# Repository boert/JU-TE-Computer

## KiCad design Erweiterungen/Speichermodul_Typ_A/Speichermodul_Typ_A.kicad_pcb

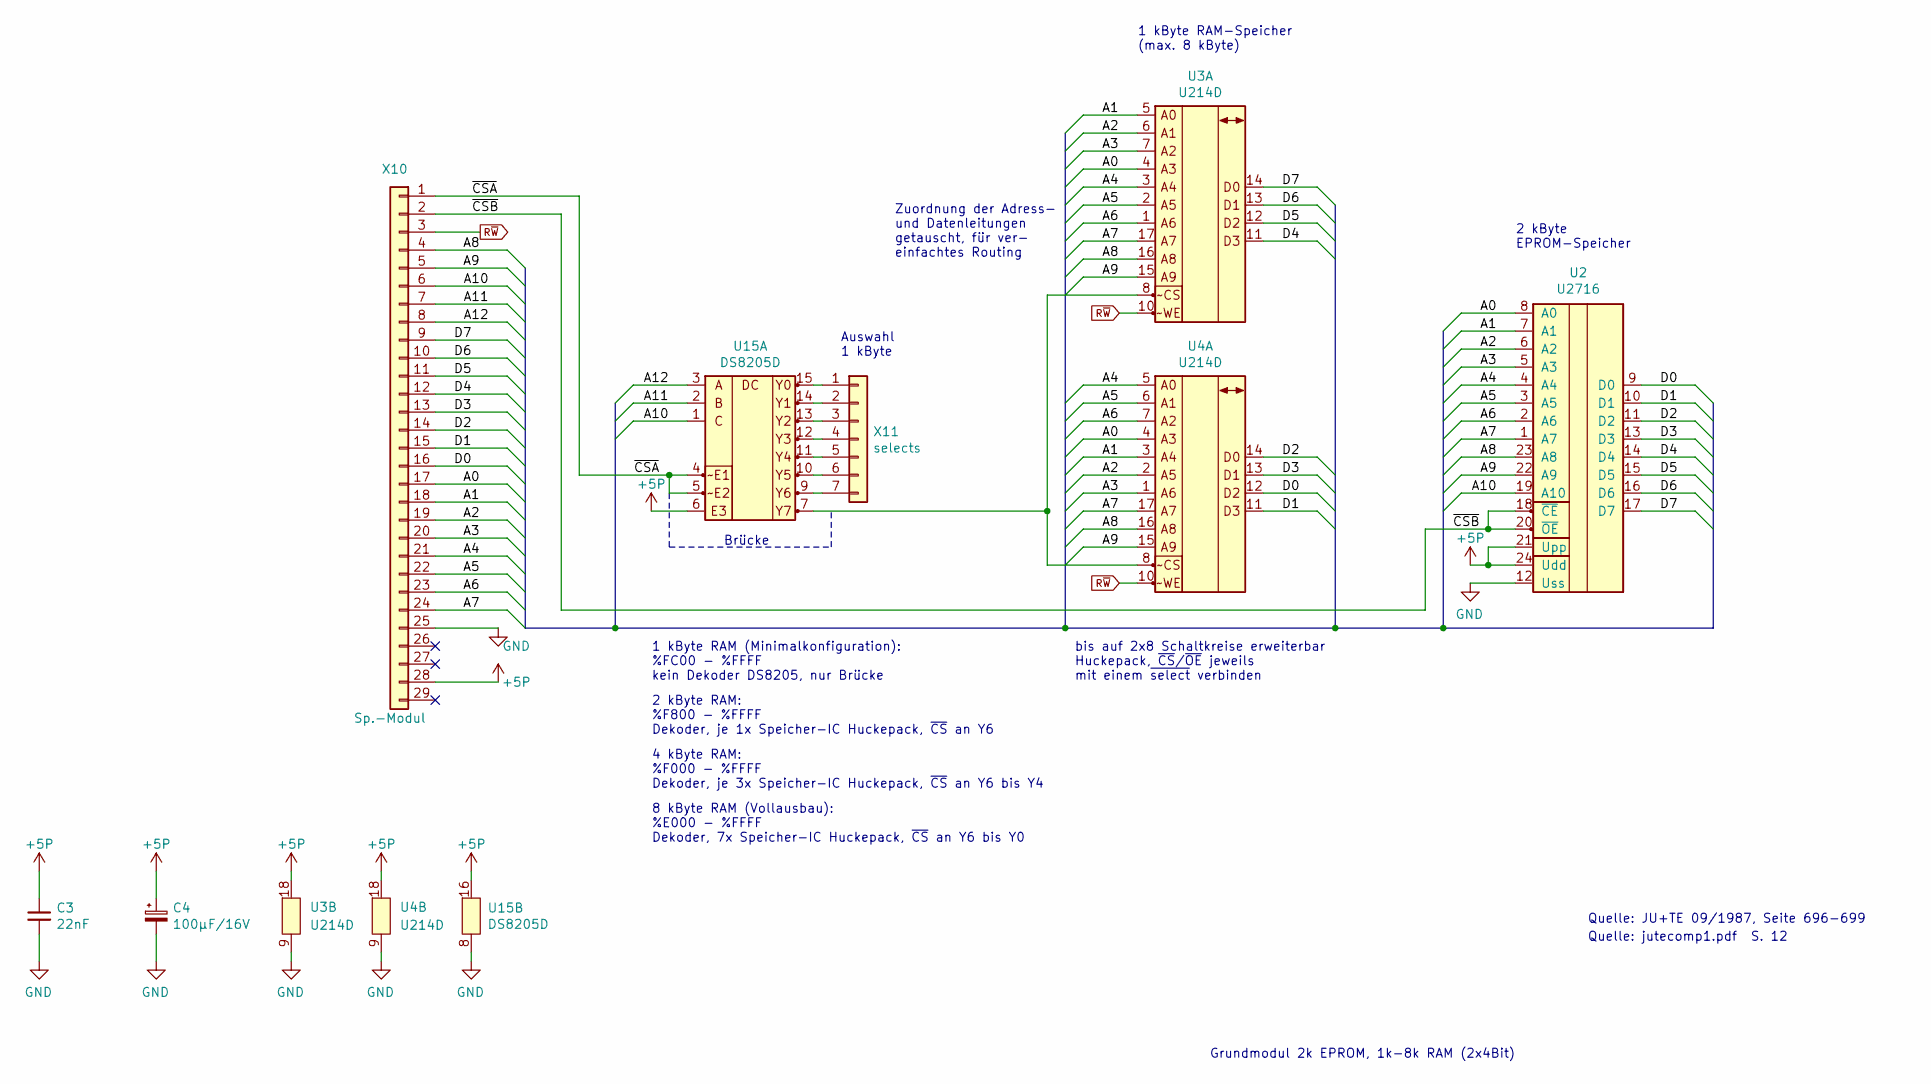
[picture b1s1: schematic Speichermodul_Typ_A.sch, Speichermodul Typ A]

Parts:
C3: 22nF; C_Disc_D4.3mm_W1.9mm_P5.00mm
C4: 100µF/16V; CP_Radial_D10.0mm_P3.50mm
U2: U2716; DIP-24_W15.24mm_Socket
U3, U4: U214D; DIP-18_W7.62mm_Socket
U15: DS8205D; DIP-16_W7.62mm_Socket
X10: Sp.-Modul; PinHeader_1x29_P2.54mm_Horizontal
X11: selects; PinSocket_1x07_P2.54mm_Vertical

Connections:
+5P: C3.1, C4.1, U2.21 (Upp), U2.24 (Udd), U3.18 (Udd), U4.18 (Udd), U15.6 (E3), U15.16 (Vcc), X10.28
/A0: U2.8 (A0), U3.4 (A3), U4.4 (A3), X10.17
/A1: U2.7 (A1), U3.5 (A0), U4.3 (A4), X10.18
/A2: U2.6 (A2), U3.6 (A1), U4.2 (A5), X10.19
/A3: U2.5 (A3), U3.7 (A2), U4.1 (A6), X10.20
/A4: U2.4 (A4), U3.3 (A4), U4.5 (A0), X10.21
/A5: U2.3 (A5), U3.2 (A5), U4.6 (A1), X10.22
/A6: U2.2 (A6), U3.1 (A6), U4.7 (A2), X10.23
/A7: U2.1 (A7), U3.17 (A7), U4.17 (A7), X10.24
/A8: U2.23 (A8), U3.16 (A8), U4.16 (A8), X10.4
/A9: U2.22 (A9), U3.15 (A9), U4.15 (A9), X10.5
/A10: U2.19 (A10), U15.1 (C), X10.6
/A11: U15.2 (B), X10.7
/A12: U15.3 (A), X10.8
/D0: U2.9 (D0), U4.12 (D2), X10.16
/D1: U2.10 (D1), U4.11 (D3), X10.15
/D2: U2.11 (D2), U4.14 (D0), X10.14
/D3: U2.13 (D3), U4.13 (D1), X10.13
/D4: U2.14 (D4), U3.11 (D3), X10.12
/D5: U2.15 (D5), U3.12 (D2), X10.11
/D6: U2.16 (D6), U3.13 (D1), X10.10
/D7: U2.17 (D7), U3.14 (D0), X10.9
/~CSA: U15.4 (~E1), U15.5 (~E2), X10.1
GND: C3.2, C4.2, U2.12 (Uss), U3.9 (Uss), U4.9 (Uss), U15.8 (GND), X10.25
unnamed: U3.8 (~CS), U4.8 (~CS), U15.7 (Y7)
unnamed: U15.9 (Y6), X11.7
unnamed: U15.10 (Y5), X11.6
unnamed: U15.11 (Y4), X11.5
unnamed: U15.12 (Y3), X11.4
unnamed: U15.13 (Y2), X11.3
unnamed: U15.14 (Y1), X11.2
unnamed: U15.15 (Y0), X11.1
R~W: U3.10 (~WE), U4.10 (~WE), X10.3
~CSB: U2.18 (~CE), U2.20 (~OE), X10.2

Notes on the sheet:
Zuordnung der Adress- und Datenleitungen getauscht, für ver- einfachtes Routing
Brücke
Quelle: JU+TE 09/1987, Seite 696-699
Quelle: jutecomp1.pdf S. 12
1 kByte RAM (Minimalkonfiguration): %FC00 - %FFFF kein Dekoder DS8205, nur Brücke
2 kByte RAM: %F800 - %FFFF Dekoder, je 1x Speicher-IC Huckepack, ~CS~ an Y6
Auswahl 1 kByte
8 kByte RAM (Vollausbau): %E000 - %FFFF Dekoder, 7x Speicher-IC Huckepack, ~CS~ an Y6 bis Y0
4 kByte RAM: %F000 - %FFFF Dekoder, je 3x Speicher-IC Huckepack, ~CS~ an Y6 bis Y4
1 kByte RAM-Speicher (max. 8 kByte)
bis auf 2x8 Schaltkreise erweiterbar Huckepack, ~CS~/~OE~ jeweils mit einem ~select~ verbinden
2 kByte EPROM-Speicher
Grundmodul 2k EPROM, 1k-8k RAM (2x4Bit)

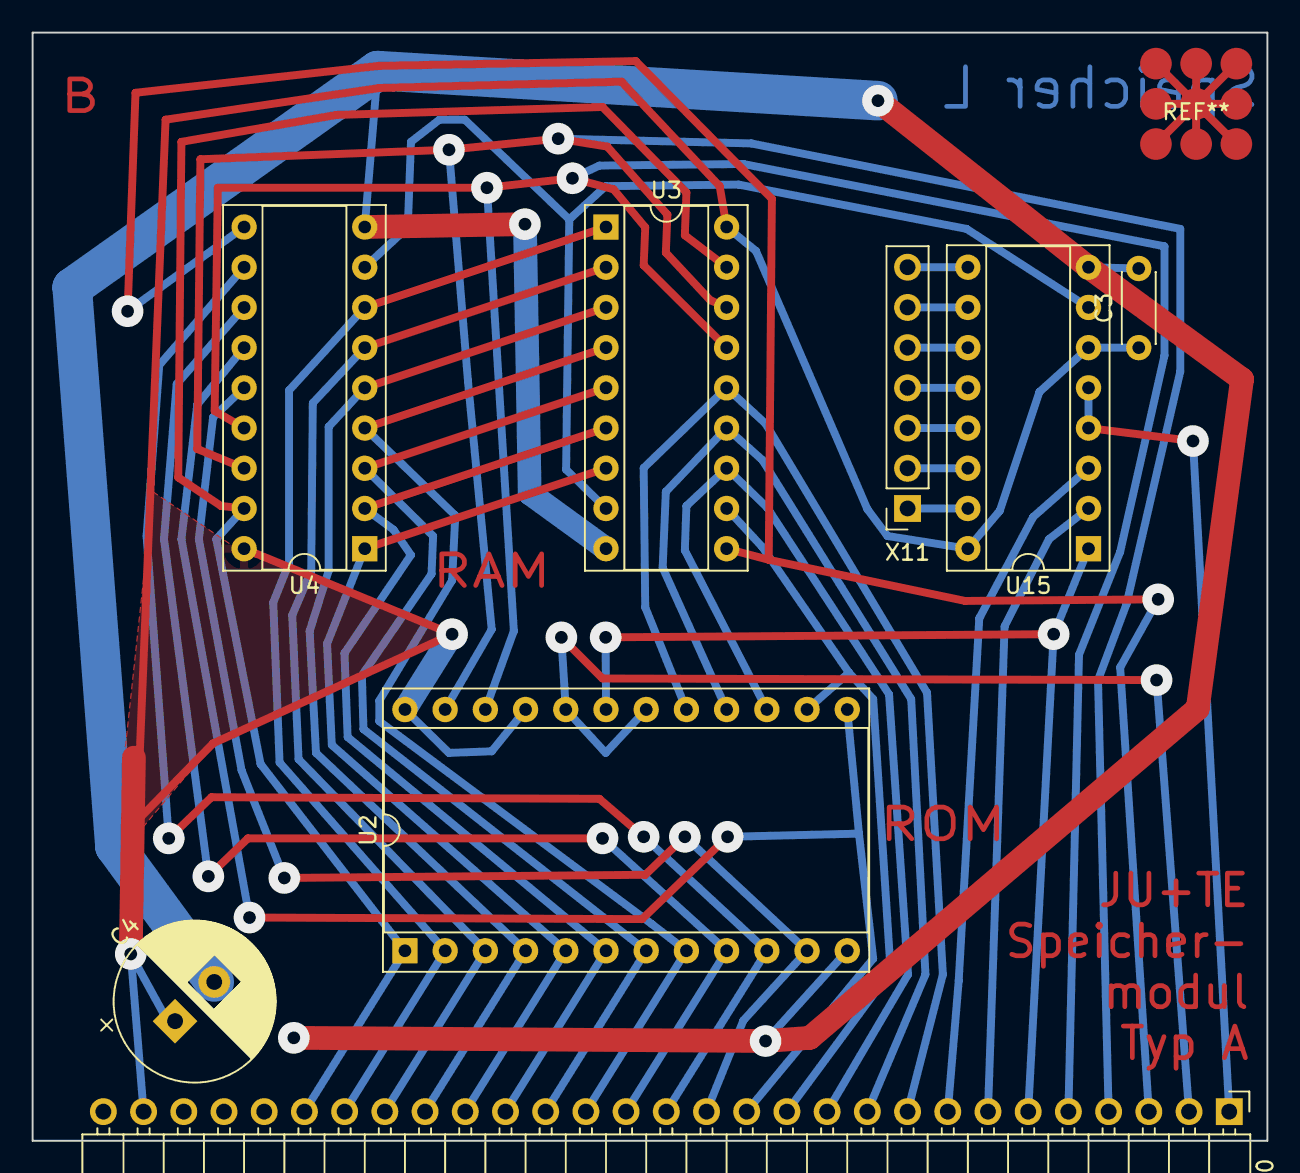
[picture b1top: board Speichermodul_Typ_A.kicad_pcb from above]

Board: 2 copper layers, 78.0 x 70.0 mm, 8 parts (0 on the bottom side), 34 nets.

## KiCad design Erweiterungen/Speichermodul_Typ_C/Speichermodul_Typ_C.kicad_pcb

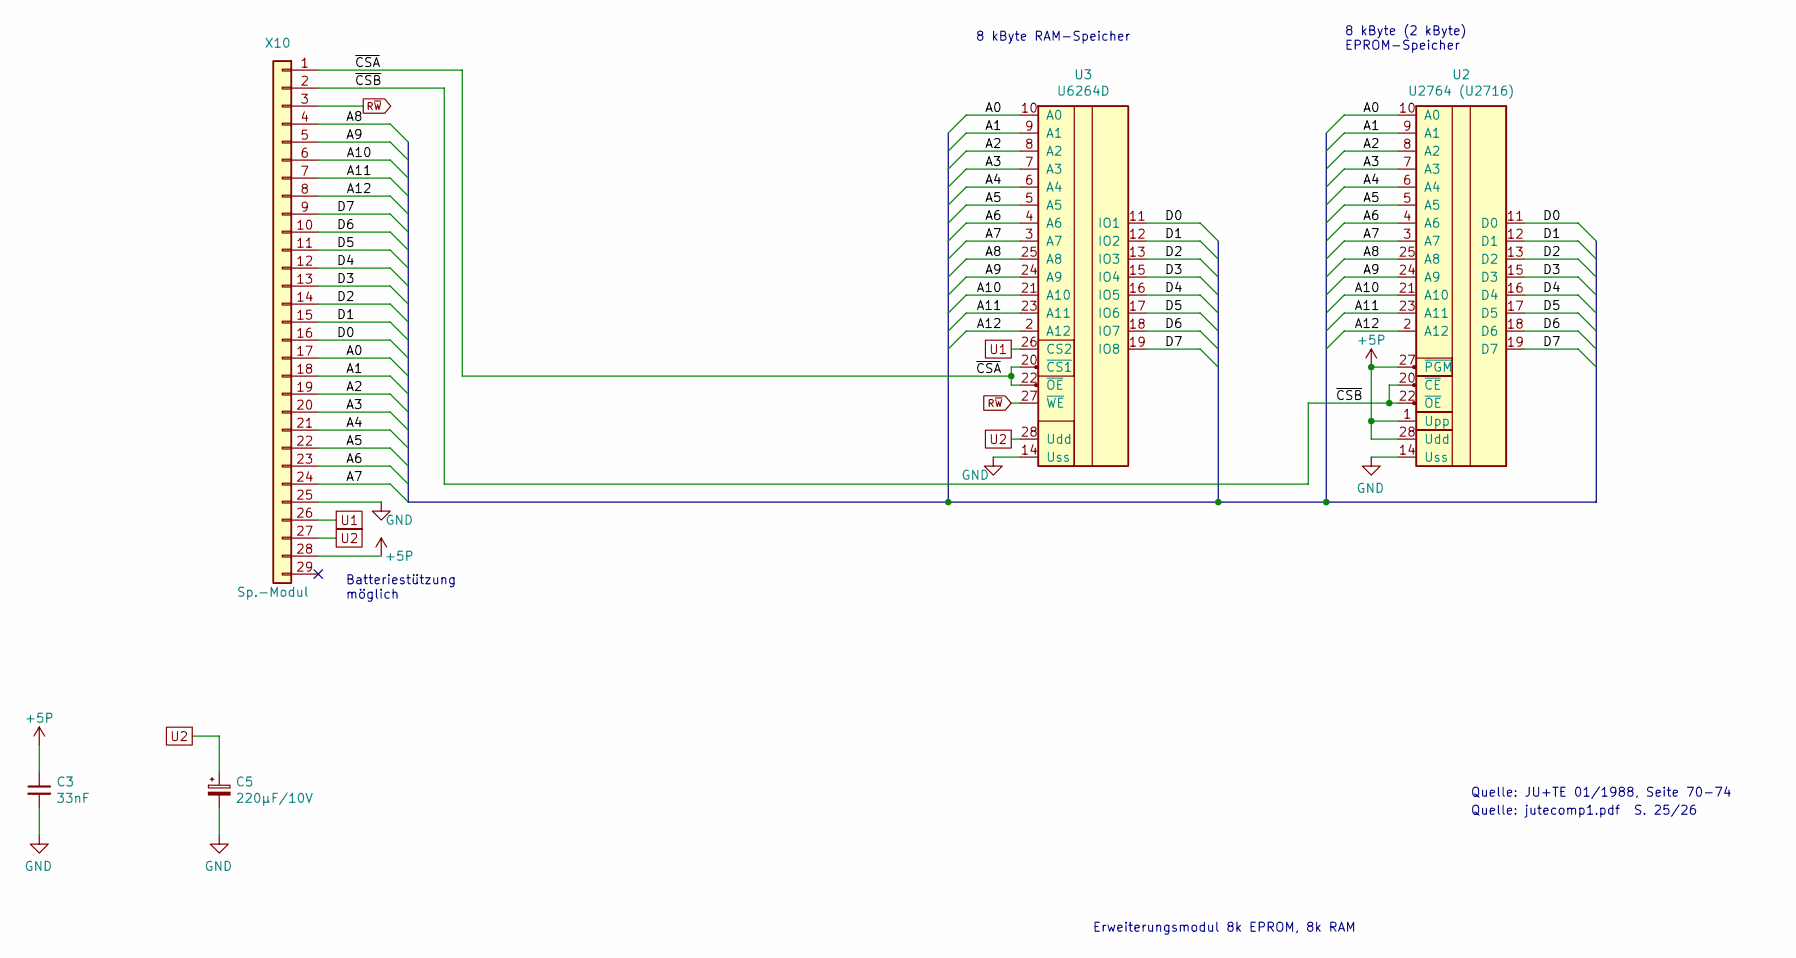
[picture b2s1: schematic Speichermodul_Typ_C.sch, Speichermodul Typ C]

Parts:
C3: 33nF; C_Disc_D4.3mm_W1.9mm_P5.00mm
C5: 220µF/10V; CP_Axial_L29.0mm_D10.0mm_P35.00mm_Horizontal
U2: U2764 (U2716); DIP-28_W15.24mm_Socket
U3: U6264D; DIP-28_W15.24mm_Socket
X10: Sp.-Modul; PinHeader_1x29_P2.54mm_Horizontal

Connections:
+5P: C3.1, U2.1 (Upp), U2.27 (~PGM), U2.28 (Udd), X10.28
/A0: U2.10 (A0), U3.10 (A0), X10.17
/A1: U2.9 (A1), U3.9 (A1), X10.18
/A2: U2.8 (A2), U3.8 (A2), X10.19
/A3: U2.7 (A3), U3.7 (A3), X10.20
/A4: U2.6 (A4), U3.6 (A4), X10.21
/A5: U2.5 (A5), U3.5 (A5), X10.22
/A6: U2.4 (A6), U3.4 (A6), X10.23
/A7: U2.3 (A7), U3.3 (A7), X10.24
/A8: U2.25 (A8), U3.25 (A8), X10.4
/A9: U2.24 (A9), U3.24 (A9), X10.5
/A10: U2.21 (A10), U3.21 (A10), X10.6
/A11: U2.23 (A11), U3.23 (A11), X10.7
/A12: U2.2 (A12), U3.2 (A12), X10.8
/D0: U2.11 (D0), U3.11 (IO1), X10.16
/D1: U2.12 (D1), U3.12 (IO2), X10.15
/D2: U2.13 (D2), U3.13 (IO3), X10.14
/D3: U2.15 (D3), U3.15 (IO4), X10.13
/D4: U2.16 (D4), U3.16 (IO5), X10.12
/D5: U2.17 (D5), U3.17 (IO6), X10.11
/D6: U2.18 (D6), U3.18 (IO7), X10.10
/D7: U2.19 (D7), U3.19 (IO8), X10.9
/~CSA: U3.20 (~CS1), U3.22 (~OE), X10.1
/~CSB: U2.20 (~CE), U2.22 (~OE), X10.2
GND: C3.2, C5.2, U2.14 (Uss), U3.14 (Uss), X10.25
R~W: U3.27 (~WE), X10.3
U1: U3.26 (CS2), X10.26
U2: C5.1, U3.28 (Udd), X10.27

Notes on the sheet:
Quelle: JU+TE 01/1988, Seite 70-74
Quelle: jutecomp1.pdf S. 25/26
Batteriestützung möglich
8 kByte RAM-Speicher
8 kByte (2 kByte) EPROM-Speicher
Erweiterungsmodul 8k EPROM, 8k RAM

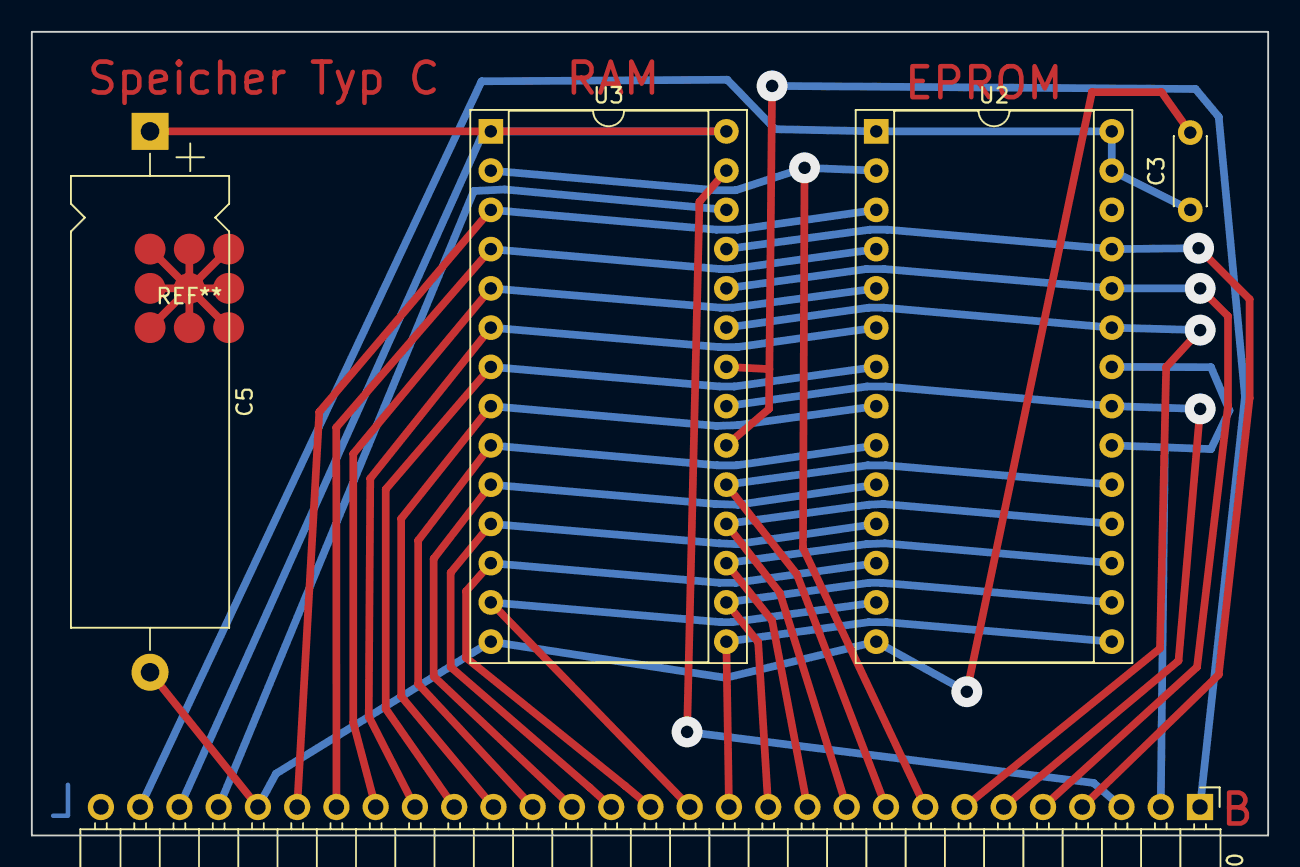
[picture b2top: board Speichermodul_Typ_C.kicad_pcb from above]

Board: 2 copper layers, 80.0 x 52.0 mm, 5 parts (0 on the bottom side), 28 nets.
